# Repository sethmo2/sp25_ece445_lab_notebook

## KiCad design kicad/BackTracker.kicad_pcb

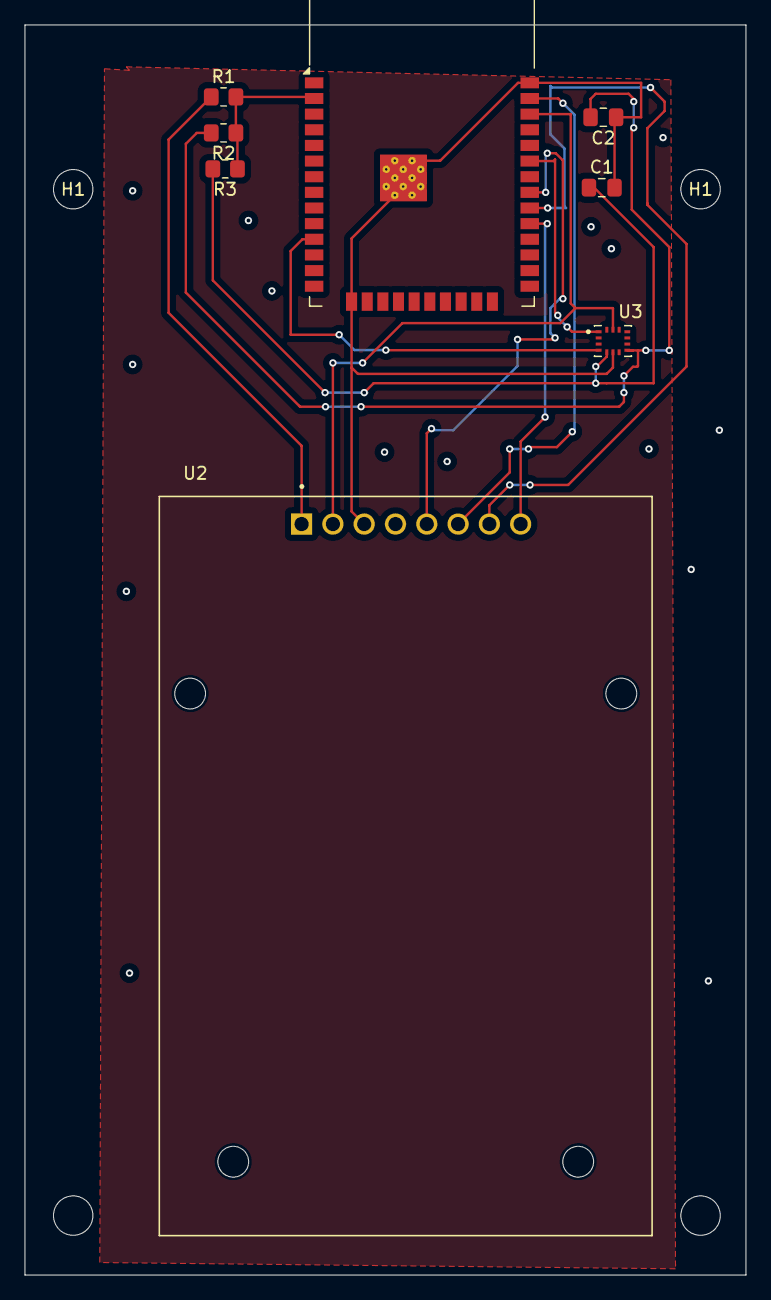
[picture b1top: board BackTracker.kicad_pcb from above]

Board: 2 copper layers, 58.5 x 101.5 mm, 12 parts (0 on the bottom side), 12 nets.

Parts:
C1, C2: 0.1uF; C_0805_2012Metric_Pad1.18x1.45mm_HandSolder
H1, H1#2, H4, H4#2: MountingHole; MountingHole_3.2mm_M3
R1: 200; R_0805_2012Metric_Pad1.20x1.40mm_HandSolder
R2, R3: 10k; R_0805_2012Metric_Pad1.20x1.40mm_HandSolder
U1: ESP32-WROOM-32D
U2: CEG006900; MODULE_CEG006900
U3: ICM-45605; XDCR_ICM-45605

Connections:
+3.3V: R1.2, R2.1, R3.1, U1.2 (VDD)
GND: C1.2, C2.1, U1.1 (GND), U1.15 (GND), U1.38 (GND), U1.39 (GND), U2.3 (GND), U3.6 (GND)
unnamed: U1.29 (IO5), U2.8 (SS/SDA/RX)
unnamed: U1.30 (IO18), U2.7 (SCK)
unnamed: U1.31 (IO19), U2.5 (MISO/SCL/TX)
unnamed: U1.33 (IO21), U3.1 (AP_SDO/AP_AD0), U3.14 (AP_SDA/AP_SDIO/AP_SDI)
unnamed: U1.36 (IO22), U2.2 (RST), U3.13 (AP_SCL/AP_SCLK)
unnamed: U1.37 (IO23), U2.6 (MOSI)
unnamed: U1.11 (IO26), U3.4 (INT1/INT)
unnamed: R1.1, U2.1 (VCC)
unnamed: C2.2, R2.2, U3.8 (VDD)
unnamed: C1.1, R3.2, U3.5 (VDDIO)

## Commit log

2025-02-18 Creating repository
2025-02-25 First notebook entry
2025-02-25 Fixed Image
2025-02-25 Fixed Spelling Error
2025-02-25 Added table of contents
2025-02-25 Added details and linked design doc
2025-03-02 02/24/25 Entry
2025-03-04 Updated Aashish and Shreyas lab notebooks
2025-03-10 Update Shreyas Worklog
2025-03-10 Added ESP32 code
2025-03-11 Adding bluetooth with nRFConnect
2025-03-12 Updated lab notebook
2025-03-12 Renamed Folder
2025-03-12 Fixed typo
2025-03-12 Added update to lab notebook
2025-03-25 Updated kicad files, fixed some errors
2025-04-03 Added KiCad files for PCB
2025-04-14 Updated KiCad .zip file
2025-04-15 More progress on Readme
2025-04-15 Working on more progress for lab
2025-04-22 Added motor attempt code
2025-04-22 Adding IMU Motor Logic code
2025-05-09 Aashish Journal
2025-05-09 Final Push
2025-05-09 Lab notebook update
